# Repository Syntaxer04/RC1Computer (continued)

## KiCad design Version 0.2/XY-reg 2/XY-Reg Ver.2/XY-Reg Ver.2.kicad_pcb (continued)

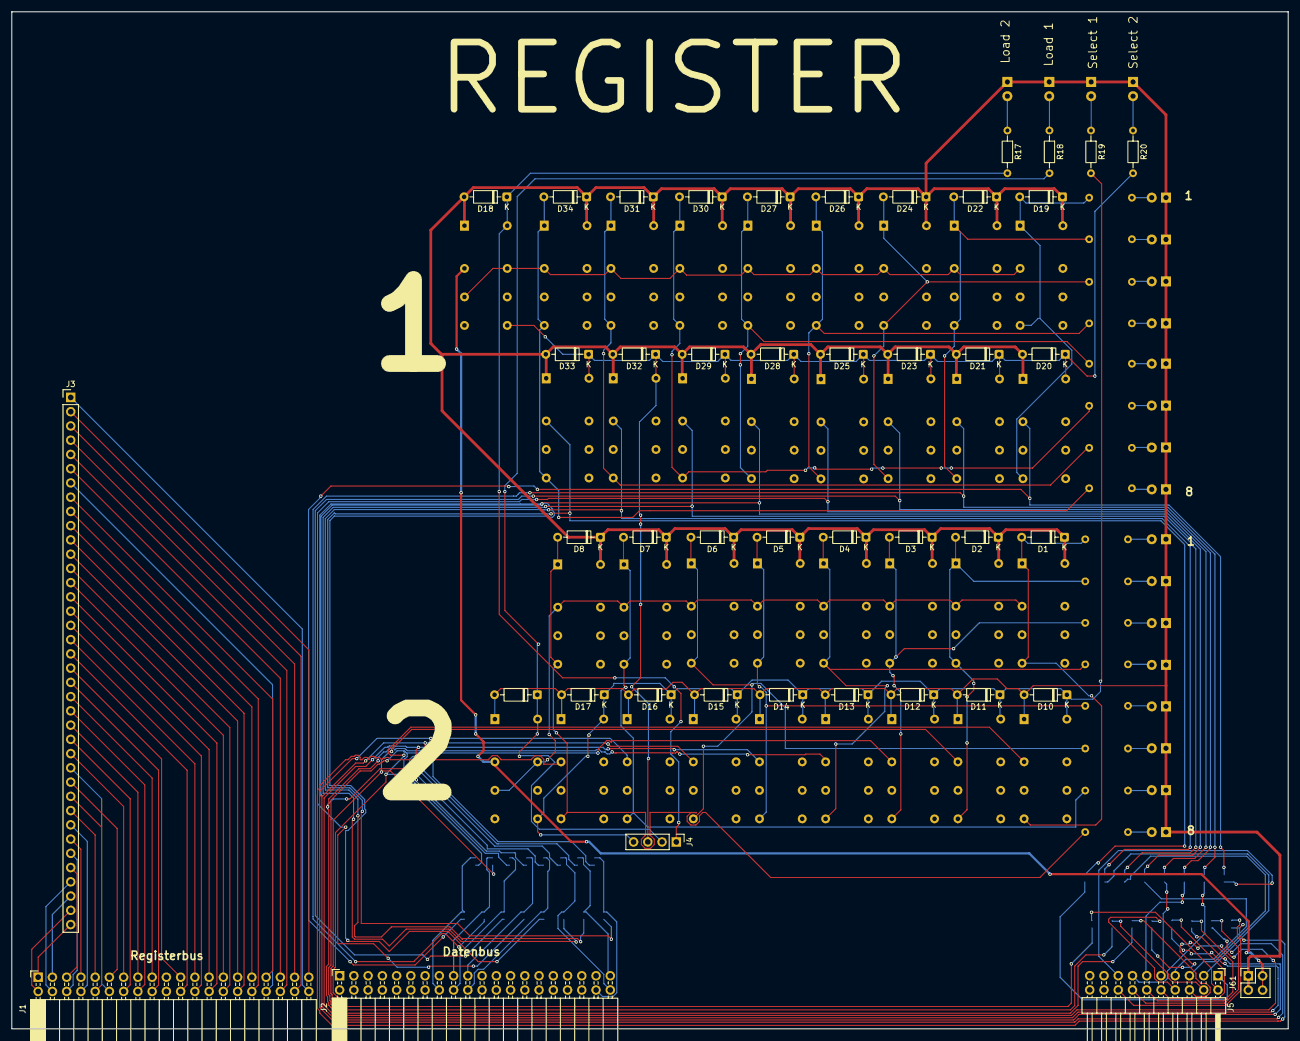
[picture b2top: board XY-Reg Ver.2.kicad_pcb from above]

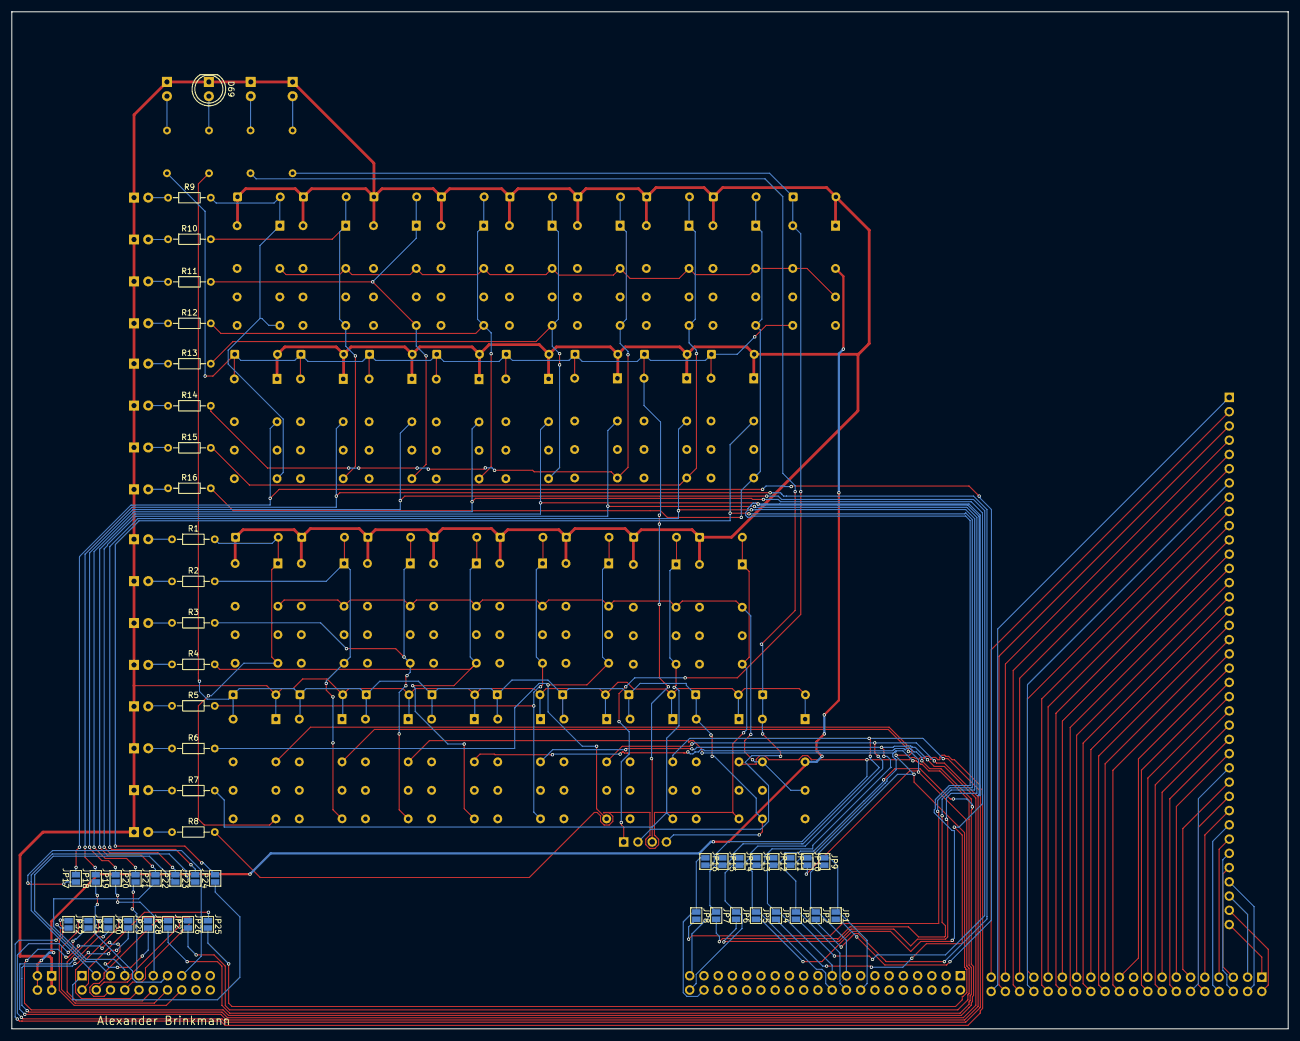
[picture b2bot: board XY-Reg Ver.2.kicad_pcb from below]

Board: 2 copper layers, 227.6 x 181.3 mm, 146 parts (68 on the bottom side), 122 nets.

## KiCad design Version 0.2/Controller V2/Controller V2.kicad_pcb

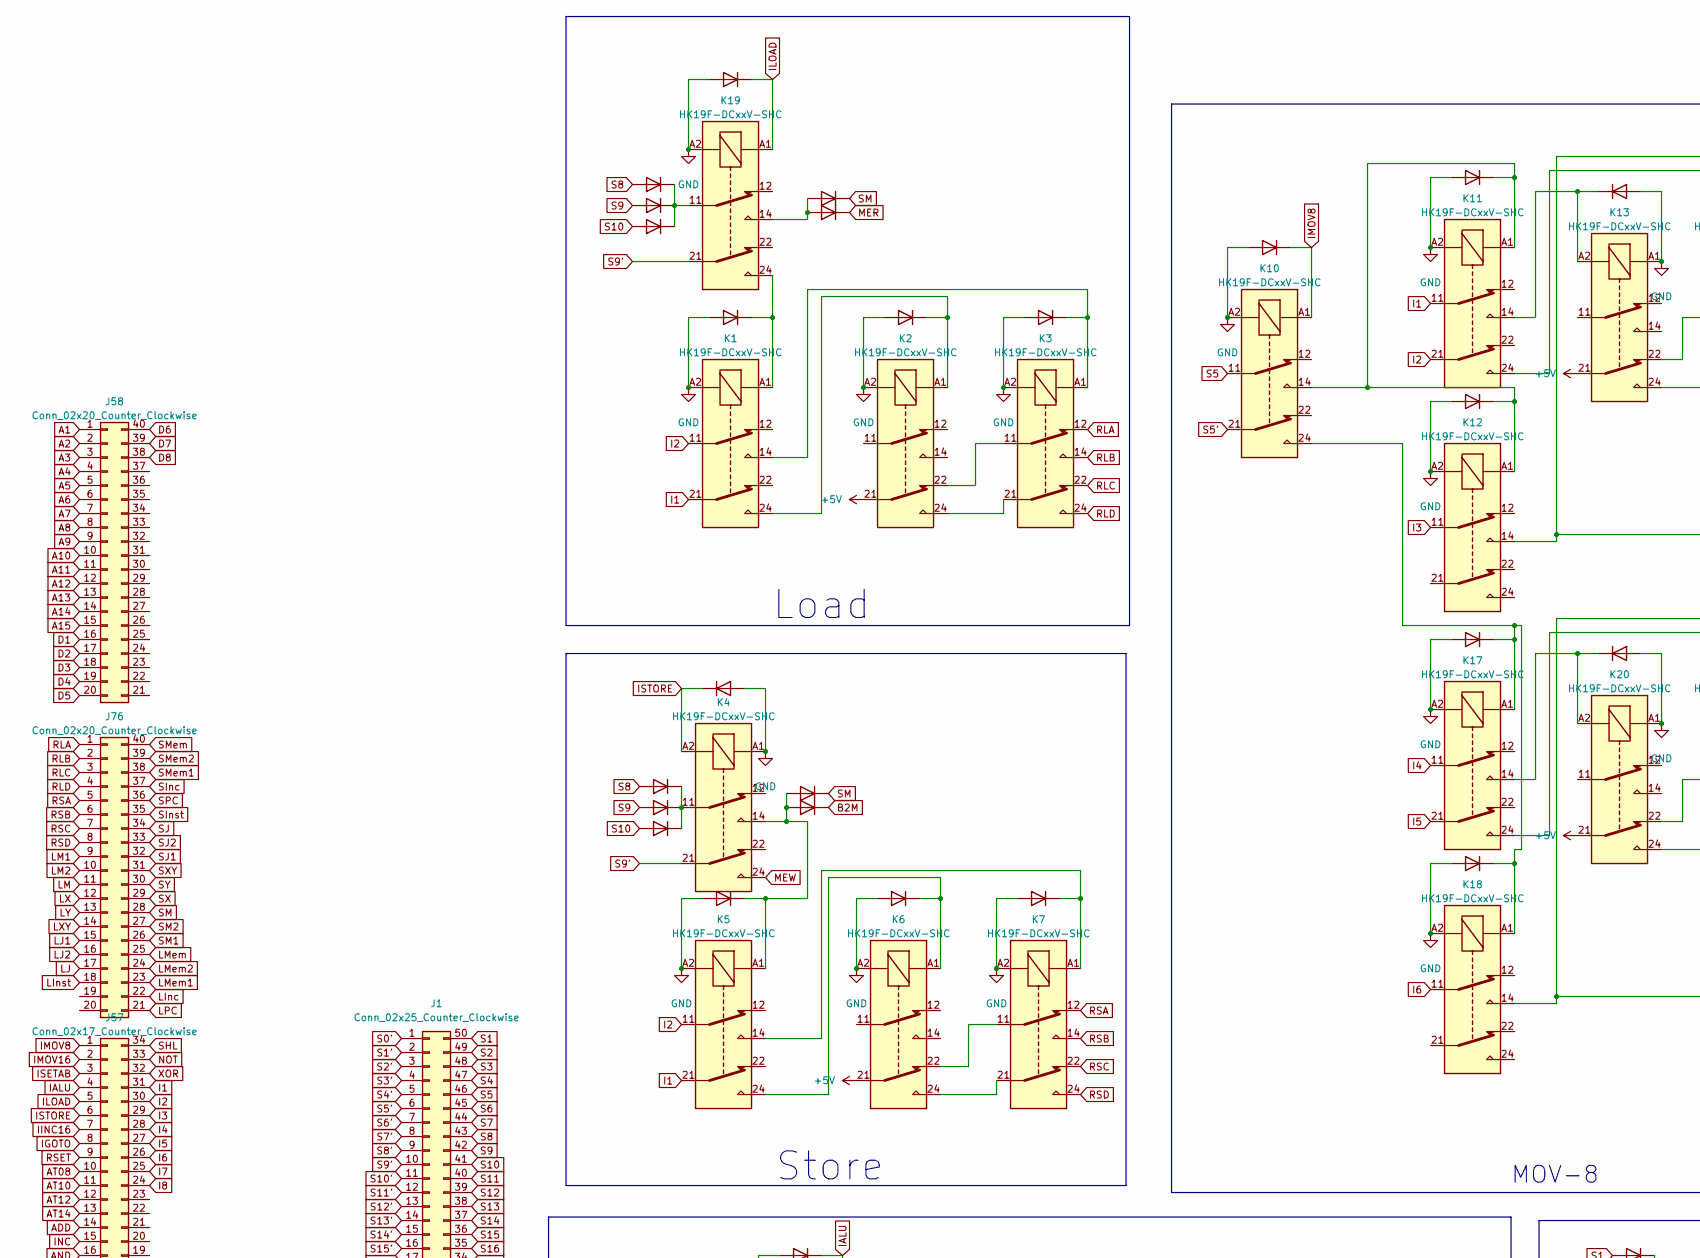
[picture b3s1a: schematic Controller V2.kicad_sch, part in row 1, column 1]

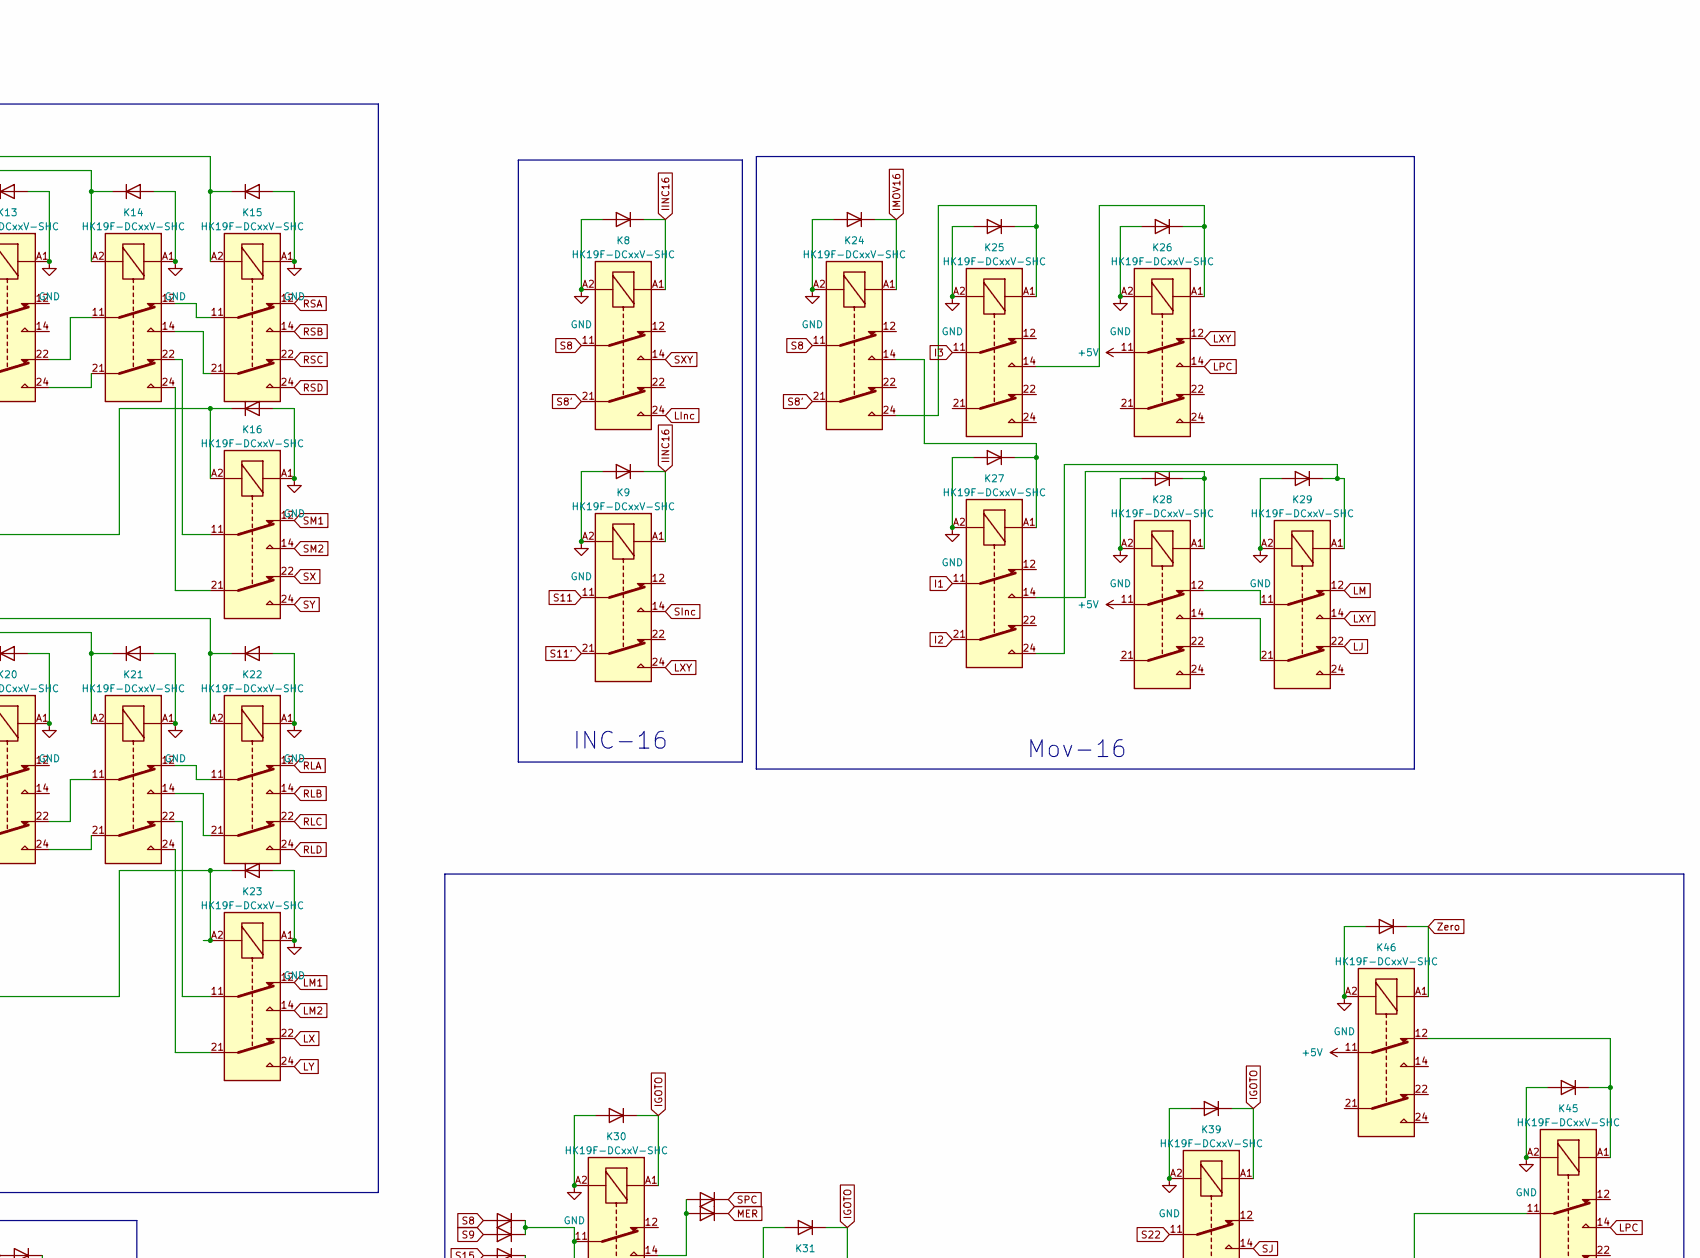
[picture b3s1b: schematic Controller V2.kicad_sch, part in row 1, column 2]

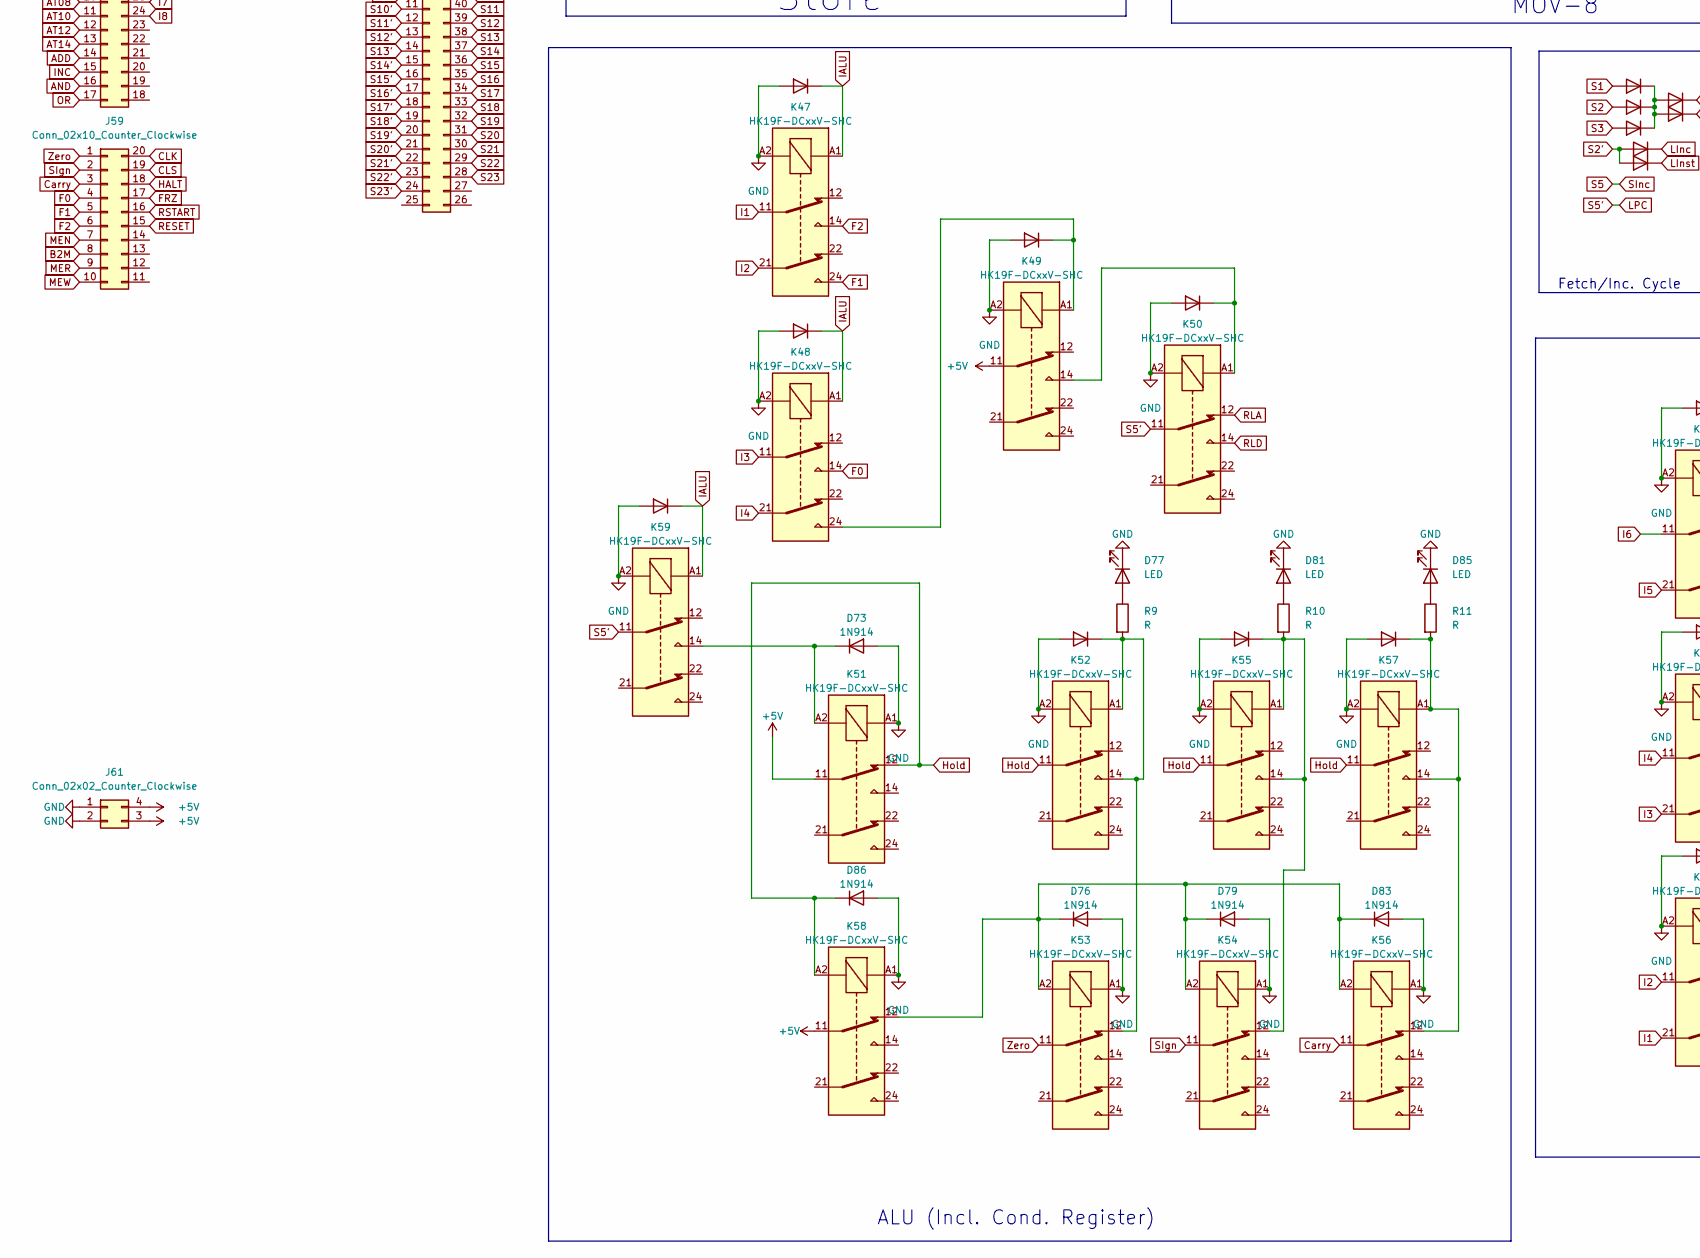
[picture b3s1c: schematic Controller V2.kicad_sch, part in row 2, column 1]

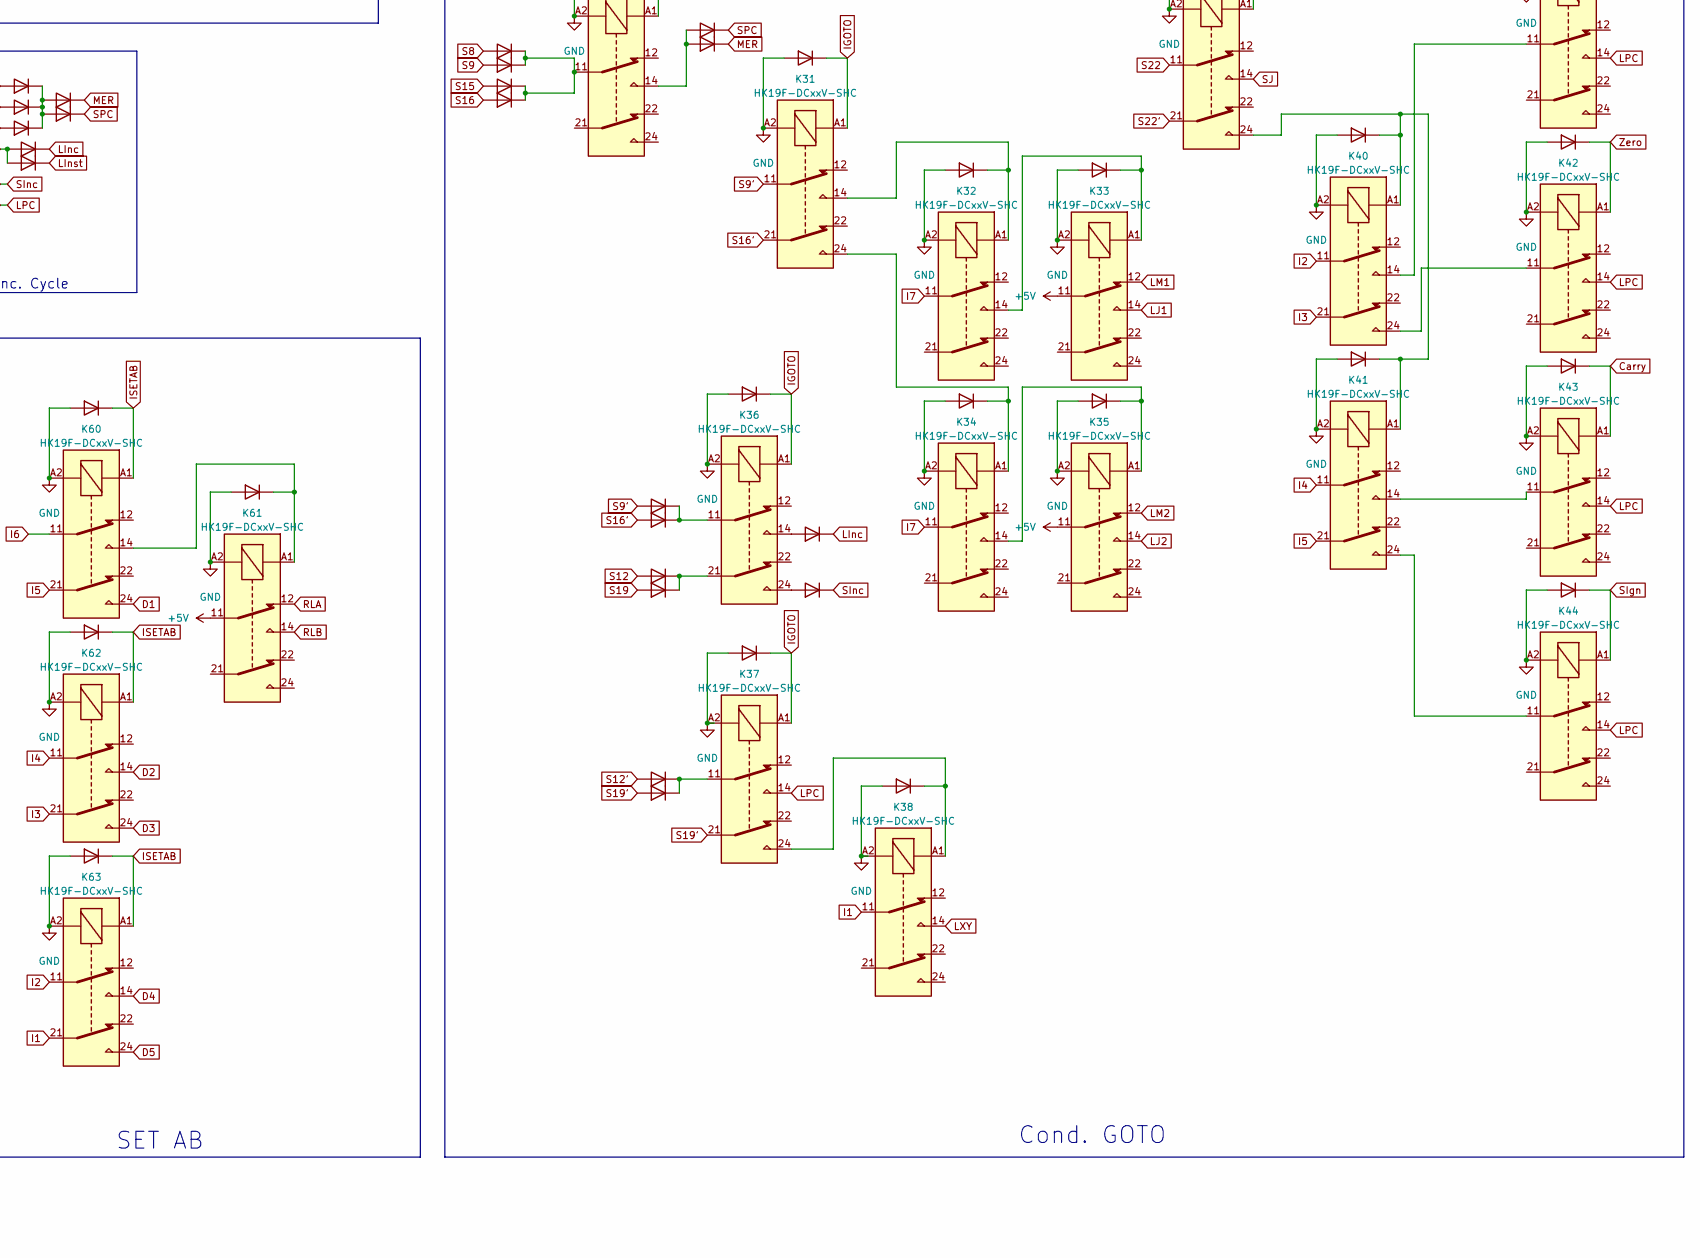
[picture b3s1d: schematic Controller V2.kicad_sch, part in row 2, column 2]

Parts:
D1, D2, D3, D4, D5, D6, D7, D8, D9, D10, D11, D12, D13, D14, D15, D16, D17, D18, D19, D20, D21, D22, D23, D24, D25, D26, D27, D28, D29, D30, D31, D32, D33, D34, D35, D36, D37, D38, D39, D40, D41, D42, D43, D44, D45, D46, D47, D48, D49, D50, D51, D52, D53, D54, D55, D56, D57, D58, D59, D60, D61, D62, D63, D64, D65, D66, D67, D68, D69, D70, D71, D72, D73, D74, D75, D76, D78, D79, D80, D82, D83, D84, D86, D87, D88, D89, D90, D91, D92, D93, D94, D95, D96, D97: 1N914; D_DO-35_SOD27_P7.62mm_Horizontal
D77, D81, D85: LED; LED_D5.0mm ohne SilkS
J1: Conn_02x25_Counter_Clockwise; PinSocket_2x25_P2.54mm_Horizontal
J57: Conn_02x17_Counter_Clockwise; PinSocket_2x17_P2.54mm_Horizontal
J58, J76: Conn_02x20_Counter_Clockwise; PinSocket_2x20_P2.54mm_Horizontal
J59: Conn_02x10_Counter_Clockwise; PinSocket_2x10_P2.54mm_Horizontal
J61: Conn_02x02_Counter_Clockwise; PinSocket_2x02_P2.54mm_Horizontal
K1, K2, K3, K4, K5, K6, K7, K8, K9, K10, K11, K12, K13, K14, K15, K16, K17, K18, K19, K20, K21, K22, K23, K24, K25, K26, K27, K28, K29, K30, K31, K32, K33, K34, K35, K36, K37, K38, K39, K40, K41, K42, K43, K44, K45, K46, K47, K48, K49, K50, K51, K52, K53, K54, K55, K56, K57, K58, K59, K60, K61, K62, K63: HK19F-DCxxV-SHC; Relay_DPDT_Finder_30.22 ohne SilkS
R9, R10, R11: R; R_Axial_DIN0204_L3.6mm_D1.6mm_P7.62mm_Horizontal

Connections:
+5V: J61.3, J61.4, K2.21, K6.21, K13.21, K20.21, K26.11, K28.11, K33.11, K35.11, K46.11, K49.11, K51.11, K58.11, K61.11
A1: J58.1
A2: J58.2
A3: J58.3
A4: J58.4
A5: J58.5
A6: J58.6
A7: J58.7
A8: J58.8
A9: J58.9
A10: J58.10
A11: J58.11
A12: J58.12
A13: J58.13
A14: J58.14
A15: J58.15
ADD: J57.14
AND: J57.16
AT08: J57.10
AT10: J57.11
AT12: J57.12
AT14: J57.13
B2M: D88.1 (K), J59.8
CLK: J59.20
CLS: J59.19
Carry: D64.1 (K), J59.3, K43.A1, K56.11
D1: J58.16, K60.24
D2: J58.17, K62.14
D3: J58.18, K62.24
D4: J58.19, K63.14
D5: J58.20, K63.24
D6: J58.40
D7: J58.39
D8: J58.38
F0: J59.4, K48.14
F1: J59.5, K47.24
F2: J59.6, K47.14
FRZ: J59.17
GND: D1.2 (A), D5.2 (A), D6.2 (A), D10.2 (A), D11.2 (A), D15.2 (A), D16.2 (A), D17.2 (A), D18.2 (A), D19.2 (A), D20.2 (A), D21.2 (A), D22.2 (A), D23.2 (A), D24.2 (A), D25.2 (A), D26.2 (A), D27.2 (A), D28.2 (A), D29.2 (A), D30.2 (A), D31.2 (A), D32.2 (A), D33.2 (A), D34.2 (A), D35.2 (A), D36.2 (A), D37.2 (A), D38.2 (A), D39.2 (A), D44.2 (A), D45.2 (A), D46.2 (A), D47.2 (A), D48.2 (A), D49.2 (A), D54.2 (A), D57.2 (A), D58.2 (A), D59.2 (A), D60.2 (A), D63.2 (A), D64.2 (A), D65.2 (A), D66.2 (A), D67.2 (A), D68.2 (A), D69.2 (A), D70.2 (A), D71.2 (A), D72.2 (A), D73.2 (A), D74.2 (A), D75.2 (A), D76.2 (A), D77.1 (K), D78.2 (A), D79.2 (A), D80.2 (A), D81.1 (K), D82.2 (A), D83.2 (A), D84.2 (A), D85.1 (K), D86.2 (A), D87.2 (A), J61.1, J61.2, K1.A2, K2.A2, K3.A2, K4.A1, K5.A2, K6.A2, K7.A2, K8.A2, K9.A2, K10.A2, K11.A2, K12.A2, K13.A1, K14.A1, K15.A1, K16.A1, K17.A2, K18.A2, K19.A2, K20.A1, K21.A1, K22.A1, K23.A1, K24.A2, K25.A2, K26.A2, K27.A2, K28.A2, K29.A2, K30.A2, K31.A2, K32.A2, K33.A2, K34.A2, K35.A2, K36.A2, K37.A2, K38.A2, K39.A2, K40.A2, K41.A2, K42.A2, K43.A2, K44.A2, K45.A2, K46.A2, K47.A2, K48.A2, K49.A2, K50.A2, K51.A1, K52.A2, K53.A1, K54.A1, K55.A2, K56.A1, K57.A2, K58.A1, K59.A2, K60.A2, K61.A2, K62.A2, K63.A2
HALT: J59.18
Hold: D86.1 (K), K51.12, K52.11, K55.11, K57.11, K58.A2
I1: J57.31, K1.21, K5.21, K11.11, K27.11, K38.11, K47.11, K63.21
I2: J57.30, K1.11, K5.11, K11.21, K27.21, K40.11, K47.21, K63.11
I3: J57.29, K12.11, K25.11, K40.21, K48.11, K62.21
I4: J57.28, K17.11, K41.11, K48.21, K62.11
I5: J57.27, K17.21, K41.21, K60.21
I6: J57.26, K18.11, K60.11
I7: J57.25, K32.11, K34.11
I8: J57.24
IALU: D68.1 (K), D69.1 (K), D74.1 (K), J57.4, K47.A1, K48.A1, K59.A1
IGOTO: D39.1 (K), D44.1 (K), D49.1 (K), D54.1 (K), D58.1 (K), J57.8, K30.A1, K31.A1, K36.A1, K37.A1, K39.A1
IINC16: D20.1 (K), D21.1 (K), J57.7, K8.A1, K9.A1
ILOAD: D19.1 (K), J57.5, K19.A1
IMOV8: D5.1 (K), J57.1, K10.A1
IMOV16: D33.1 (K), J57.2, K24.A1
INC: J57.15
ISETAB: D72.1 (K), D82.1 (K), D87.1 (K), J57.3, K60.A1, K62.A1, K63.A1
ISTORE: D18.1 (K), J57.6, K4.A2
LInc: D62.1 (K), D96.1 (K), J76.22, K8.24
LInst: D97.1 (K), J76.18
LJ1: J76.15, K33.14
LJ2: J76.16, K35.14
LJ: J76.17, K29.22
LM: J76.11, K29.12
LM1: J76.9, K23.12, K33.12
LM2: J76.10, K23.14, K35.12
LMem: J76.25
LMem1: J76.23
LMem2: J76.24
LPC: J1.6, J76.21, K10.21, K26.14, K37.14, K42.14, K43.14, K44.14, K45.14, K50.11, K59.11
LX: J76.12, K23.22
LXY: J76.14, K9.24, K26.12, K29.14, K38.14
LY: J76.13, K23.24
MEN: J59.7
MER: D91.1 (K), D92.1 (K), D95.1 (K), J59.9
MEW: J59.10, K4.24
NOT: J57.33
unnamed: D1.1 (K), K1.A1, K19.24
unnamed: D2.1 (K), D3.1 (K), D4.1 (K), D92.2 (A), D93.2 (A)
unnamed: D7.1 (K), D8.1 (K), D9.1 (K), K19.11
unnamed: D10.1 (K), K1.24, K2.A1
unnamed: D11.1 (K), K1.14, K3.A1
unnamed: D12.1 (K), D13.1 (K), D14.1 (K), K4.11
unnamed: D15.1 (K), D88.2 (A), D89.2 (A), K4.14, K5.A1
unnamed: D16.1 (K), K5.24, K6.A1
unnamed: D17.1 (K), K5.14, K7.A1
unnamed: D6.1 (K), D22.1 (K), K10.14, K11.A1, K12.A1
unnamed: D23.1 (K), K11.14, K13.A2
unnamed: D24.1 (K), K11.24, K14.A2
unnamed: D25.1 (K), D26.1 (K), K12.14, K15.A2, K16.A2
unnamed: D27.1 (K), D28.1 (K), K10.24, K17.A1, K18.A1
unnamed: D29.1 (K), K17.14, K20.A2
unnamed: D30.1 (K), K17.24, K21.A2
unnamed: D31.1 (K), D32.1 (K), K18.14, K22.A2, K23.A2
unnamed: D34.1 (K), K24.24, K25.A1
unnamed: D35.1 (K), K25.14, K26.A1
unnamed: D36.1 (K), K24.14, K27.A1
unnamed: D37.1 (K), K27.14, K28.A1
unnamed: D38.1 (K), K27.24, K29.A1
unnamed: D40.1 (K), D41.1 (K), D42.1 (K), D43.1 (K), K30.11
unnamed: D45.1 (K), K31.14, K32.A1
unnamed: D46.1 (K), K32.14, K33.A1
unnamed: D47.1 (K), K31.24, K34.A1
unnamed: D48.1 (K), K34.14, K35.A1
unnamed: D50.1 (K), D51.1 (K), K36.11
unnamed: D52.1 (K), D53.1 (K), K36.21
unnamed: D55.1 (K), D56.1 (K), K37.11
unnamed: D57.1 (K), K37.24, K38.A1
unnamed: D59.1 (K), D60.1 (K), K39.24, K40.A1, K41.A1
unnamed: D61.2 (A), K36.24
unnamed: D62.2 (A), K36.14
unnamed: D66.1 (K), K45.A1, K46.12
unnamed: D70.1 (K), K48.24, K49.A1
unnamed: D71.1 (K), K49.14, K50.A1
unnamed: D73.1 (K), K51.A2, K59.14
unnamed: D75.1 (K), K52.14, K52.A1, K53.12, R9.2
unnamed: D76.1 (K), D79.1 (K), D83.1 (K), K53.A2, K54.A2, K56.A2, K58.12
unnamed: D77.2 (A), R9.1
unnamed: D78.1 (K), K60.14, K61.A1
unnamed: D80.1 (K), K54.12, K55.14, K55.A1, R10.2
unnamed: D81.2 (A), R10.1
unnamed: D84.1 (K), K56.12, K57.14, K57.A1, R11.2
unnamed: D85.2 (A), R11.1
unnamed: D90.2 (A), D91.2 (A), K19.14
unnamed: D94.2 (A), D95.2 (A), K30.14
unnamed: K2.22, K3.11
unnamed: K2.24, K3.21
unnamed: K6.22, K7.11
unnamed: K6.24, K7.21
unnamed: K13.22, K14.11
unnamed: K13.24, K14.21
unnamed: K14.12, K15.11
unnamed: K14.14, K15.21
unnamed: K14.22, K16.11
unnamed: K14.24, K16.21
unnamed: K20.22, K21.11
unnamed: K20.24, K21.21
unnamed: K21.12, K22.11
unnamed: K21.14, K22.21
unnamed: K21.22, K23.11
unnamed: K21.24, K23.21
unnamed: K28.12, K29.11
unnamed: K28.14, K29.21
unnamed: K40.14, K45.11
unnamed: K40.24, K42.11
unnamed: K41.14, K43.11
unnamed: K41.24, K44.11
OR: J57.17
RESET: J59.15
RLA: J76.1, K3.12, K22.12, K50.12, K61.12
RLB: J76.2, K3.14, K22.14, K61.14
RLC: J76.3, K3.22, K22.22
RLD: J76.4, K3.24, K22.24, K50.14
RSA: J76.5, K7.12, K15.12
RSB: J76.6, K7.14, K15.14
RSC: J76.7, K7.22, K15.22
RSD: J76.8, K7.24, K15.24
RSET: J57.9
RSTART: J59.16
S0': J1.1
S1: D2.2 (A), J1.50
S1': J1.2
S2: D3.2 (A), J1.49
S2': D96.2 (A), D97.2 (A), J1.3
S3: D4.2 (A), J1.48
S3': J1.4
S4: J1.47
S4': J1.5
S5: D61.1 (K), J1.46, J76.37, K9.14, K10.11
S6: J1.45
S6': J1.7
S7: J1.44
S7': J1.8
S8: D7.2 (A), D12.2 (A), D40.2 (A), J1.43, K8.11, K24.11
S8': J1.9, K8.21, K24.21
S9: D8.2 (A), D13.2 (A), D41.2 (A), J1.42
S9': D50.2 (A), J1.10, K4.21, K19.21, K31.11
S10: D9.2 (A), D14.2 (A), J1.41
S10': J1.11
S11: J1.40, K9.11
S11': J1.12, K9.21
S12: D52.2 (A), J1.39
S12': D55.2 (A), J1.13
S13: J1.38
S13': J1.14
S14: J1.37
S14': J1.15
S15: D42.2 (A), J1.36
S15': J1.16
S16: D43.2 (A), J1.35
S16': D51.2 (A), J1.17, K31.21
S17: J1.34
S17': J1.18
S18: J1.33
S18': J1.19
S19: D53.2 (A), J1.32
S19': D56.2 (A), J1.20, K37.21
S20: J1.31
S20': J1.21
S21: J1.30
S21': J1.22
S22: J1.29, K39.11
S22': J1.23, K39.21
S23: J1.28
S23': J1.24
SHL: J57.34
SIgn: D65.1 (K), J59.2, K44.A1, K54.11
SInst: J76.35
SJ1: J76.32
SJ2: J76.33
SJ: J76.34, K39.14
SM: D89.1 (K), D90.1 (K), J76.28
SM1: J76.26, K16.12
SM2: J76.27, K16.14
SMem: J76.40
SMem1: J76.38
SMem2: J76.39
SPC: D93.1 (K), D94.1 (K), J76.36
SX: J76.29, K16.22
SXY: J76.31, K8.14
SY: J76.30, K16.24
XOR: J57.32
Zero: D63.1 (K), D67.1 (K), J59.1, K42.A1, K46.A1, K53.11

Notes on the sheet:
SET AB
Fetch/Inc. Cycle
ALU (Incl. Cond. Register)
Cond. GOTO
Load
Mov-16
MOV-8
INC-16
Store

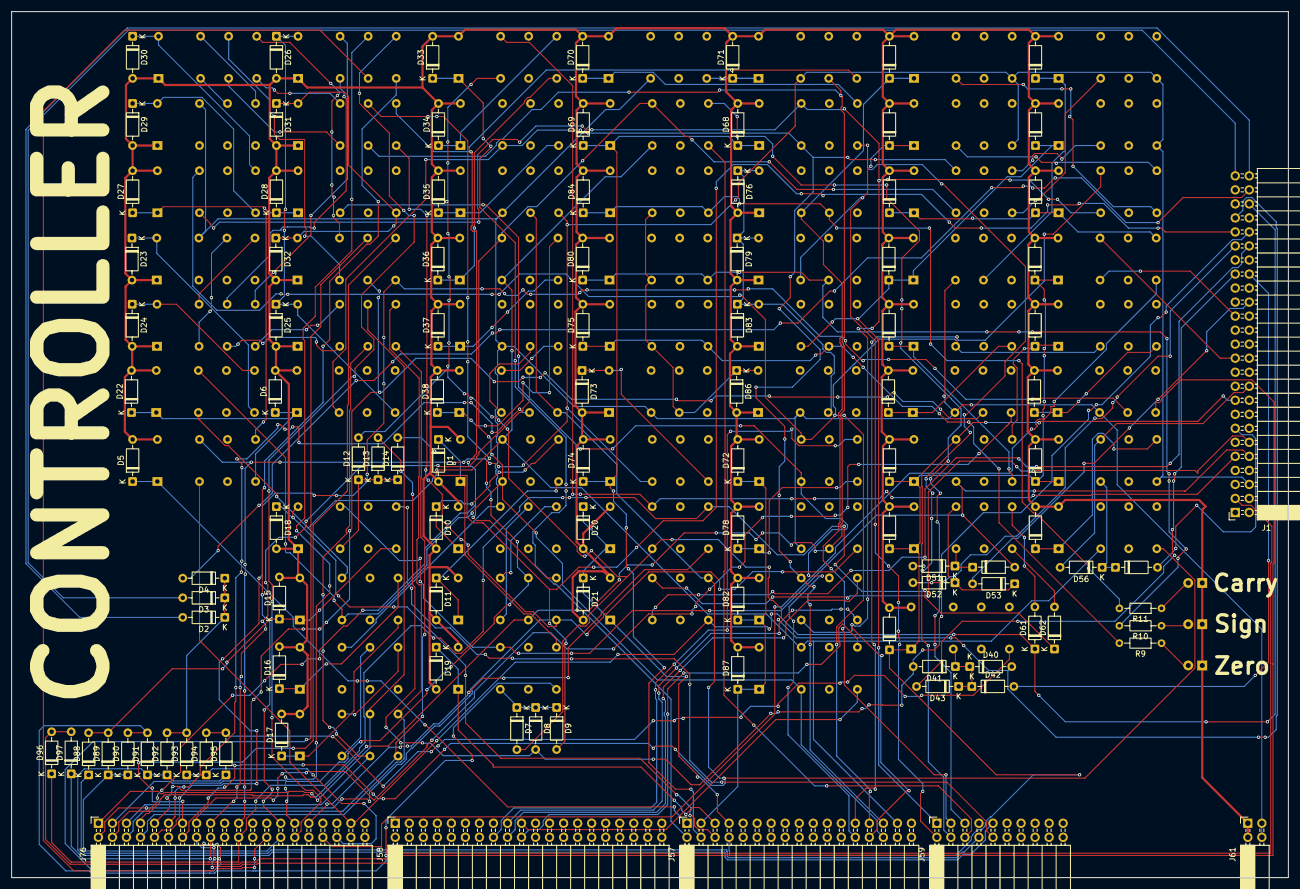
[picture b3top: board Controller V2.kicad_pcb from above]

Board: 2 copper layers, 231.2 x 156.8 mm, 169 parts (0 on the bottom side), 151 nets.
